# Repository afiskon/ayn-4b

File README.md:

# AYN/4B

Portable QRP CW Transceiver

* Covers 40, 30, 20 and 17 meters
* Classical single IF superheterodyne design
* Has just a few barely hearable (~S0) spurious signals
* Simple but effective AGC
* Supports RIT and XIT
* 10-30 WPM Elekey-B type keyer + straight key mode
* Keyer supports record and playback, programmable with paddles
* ~5W class D power amplifier
* Has a VCC indicator and a SWR meter
* PCB is designed to fit into Hammond 1590BB enclosure
* The project is 100% open-source

Links:
* Article (in Russian): https://eax.me/2023/2023-05-01-ayn-4b-transceiver.html
* Demo: https://www.youtube.com/watch?v=IM0qo4IA7QQ
* Fork by Kirill, R2AXZ with CMake support: https://github.com/r2axz/ayn-4b

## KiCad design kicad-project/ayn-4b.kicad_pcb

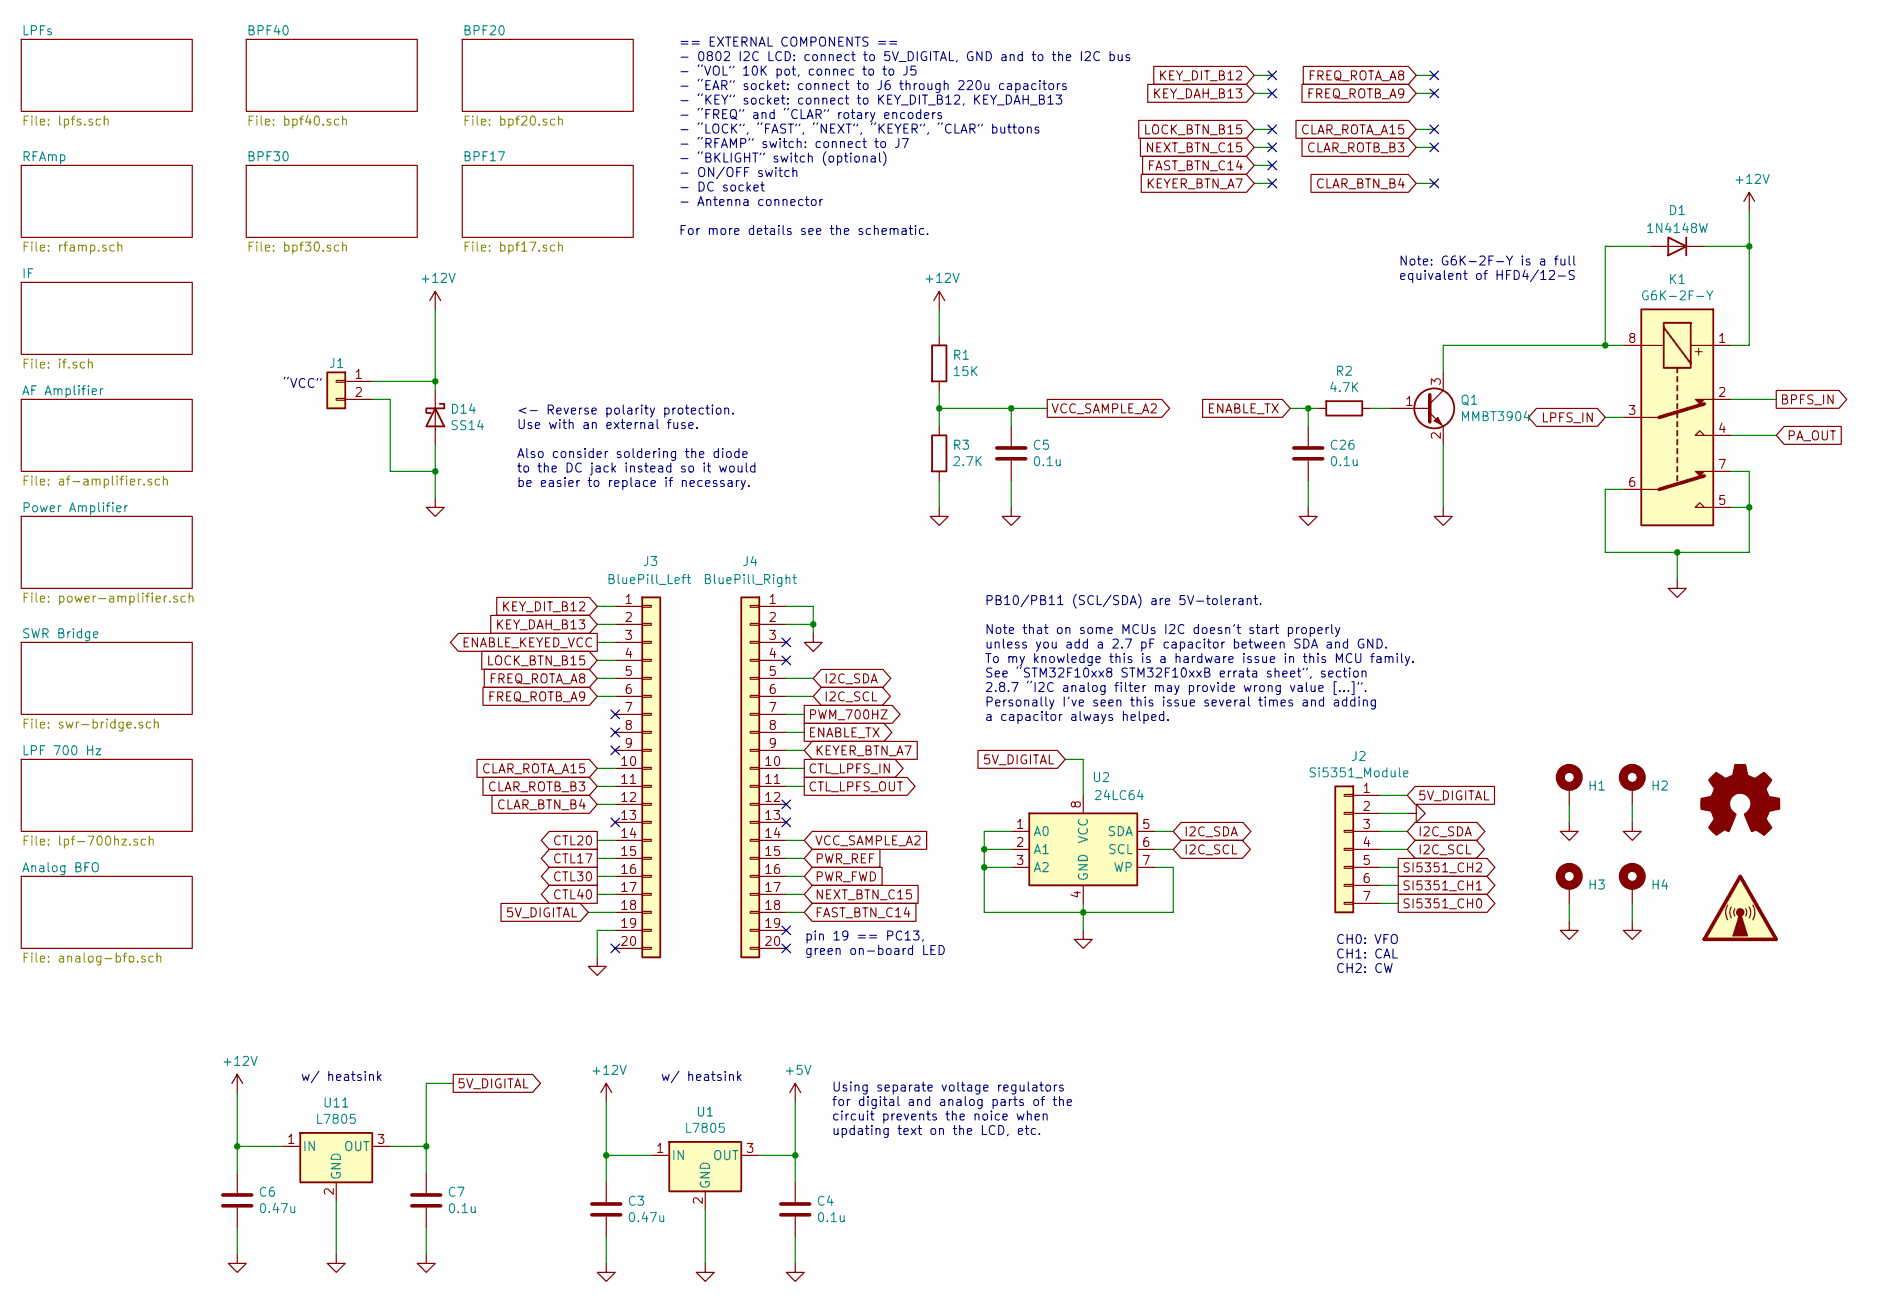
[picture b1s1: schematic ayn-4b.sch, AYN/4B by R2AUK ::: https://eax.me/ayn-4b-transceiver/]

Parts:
C3, C6: 0.47u; C_0805_2012Metric_Pad1.15x1.40mm_HandSolder
C4, C5, C7, C26: 0.1u; C_0805_2012Metric_Pad1.15x1.40mm_HandSolder
D1: 1N4148W; D_SOD-123
D14: SS14; D_SMA_Handsoldering
H1, H2, H3, H4: MountingHole_Pad; MountingHole_M3_Pad_Large
J1: Conn_01x02; PinSocket_1x02_P2.54mm_Vertical
J2: Si5351_Module; PinSocket_1x07_P2.54mm_Vertical
J3: BluePill_Left; PinSocket_1x20_P2.54mm_Vertical
J4: BluePill_Right; PinSocket_1x20_P2.54mm_Vertical
K1: G6K-2F-Y; Relay_DPDT_Omron_G6K-2F-Y
Q1: MMBT3904; SOT-23
R1: 15K; R_0805_2012Metric_Pad1.15x1.40mm_HandSolder
R2: 4.7K; R_0805_2012Metric_Pad1.15x1.40mm_HandSolder
R3: 2.7K; R_0805_2012Metric_Pad1.15x1.40mm_HandSolder
SYM1: Logo_Open_Hardware_Small; OSHW-Logo2_14.6x12mm_SilkScreen
SYM2: SYM_Radio_Waves_Large; KiCad-Logo_5mm_SilkScreen
U1: L7805; TO-220-3_Vertical
U2: 24LC64; SO-8_5.3x6.2mm_P1.27mm
U11: L7805; TO-263-2

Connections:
5V_DIGITAL: C7.1, J2.1, J3.18, U2.8 (VCC), U11.3 (OUT)
+5V: C4.1, U1.3 (OUT); also elsewhere on the board
+12V: C3.1, C6.1, D1.1 (K), D14.1 (K), J1.1, K1.1, R1.1, U1.1 (IN), U11.1 (IN); also elsewhere on the board
BPFS_IN: K1.2; also elsewhere on the board
CLAR_BTN_B4: J3.12
CLAR_ROTA_A15: J3.10
CLAR_ROTB_B3: J3.11
CTL17: J3.15; also elsewhere on the board
CTL20: J3.14; also elsewhere on the board
CTL30: J3.16; also elsewhere on the board
CTL40: J3.17; also elsewhere on the board
CTL_LPFS_IN: J4.10; also elsewhere on the board
CTL_LPFS_OUT: J4.11; also elsewhere on the board
ENABLE_KEYED_VCC: J3.3; also elsewhere on the board
ENABLE_TX: C26.1, J4.8, R2.2
FAST_BTN_C14: J4.18
FREQ_ROTA_A8: J3.5
FREQ_ROTB_A9: J3.6
GND: C3.2, C4.2, C5.2, C6.2, C7.2, C26.2, D14.2 (A), H1.1, H2.1, H3.1, H4.1, J1.2, J2.2, J3.19, J4.1, J4.2, K1.5, K1.6, K1.7, Q1.2 (E), R3.2, U1.2 (GND), U2.1 (A0), U2.2 (A1), U2.3 (A2), U2.4 (GND), U2.7 (WP), U11.2 (GND); also elsewhere on the board
I2C_SCL: J2.4, J4.6, U2.6 (SCL)
I2C_SDA: J2.3, J4.5, U2.5 (SDA)
KEYER_BTN_A7: J4.9
KEY_DAH_B13: J3.2
KEY_DIT_B12: J3.1
LOCK_BTN_B15: J3.4
LPFS_IN: K1.3; also elsewhere on the board
NEXT_BTN_C15: J4.17
unnamed: D1.2 (A), K1.8, Q1.3 (C)
unnamed: Q1.1 (B), R2.1
PA_OUT: K1.4; also elsewhere on the board
PWM_700HZ: J4.7; also elsewhere on the board
PWR_FWD: J4.16; also elsewhere on the board
PWR_REF: J4.15; also elsewhere on the board
SI5351_CH0: J2.7; also elsewhere on the board
SI5351_CH1: J2.6
SI5351_CH2: J2.5; also elsewhere on the board
VCC_SAMPLE_A2: C5.1, J4.14, R1.2, R3.1

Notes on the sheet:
CH0: VFO CH1: CAL CH2: CW
== EXTERNAL COMPONENTS == - 0802 I2C LCD: connect to 5V_DIGITAL, GND and to the I2C bus - “VOL” 10K pot, connec to to J5 - “EAR” socket: connect to J6 through 220u capacitors - “KEY” socket: connect to KEY_DIT_B12, KEY_DAH_B13 - “FREQ” and “CLAR” rotary encoders - “LOCK”, “FAST”, “NEXT”, “KEYER”, “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
w/ heatsink
Note: G6K-2F-Y is a full equivalent of HFD4/12-S
<- Reverse polarity protection. Use with an external fuse. Also consider soldering the diode to the DC jack instead so it would be easier to replace if necessary.
Using separate voltage regulators for digital and analog parts of the circuit prevents the noice when updating text on the LCD, etc.
“VCC”
PB10/PB11 (SCL/SDA) are 5V-tolerant. Note that on some MCUs I2C doesn’t start properly unless you add a 2.7 pF capacitor between SDA and GND. To my knowledge this is a hardware issue in this MCU family. See “STM32F10xx8 STM32F10xxB errata sheet”, section 2.8.7 “I2C analog filter may provide wrong v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
pin 19 == PC13, green on-board LED

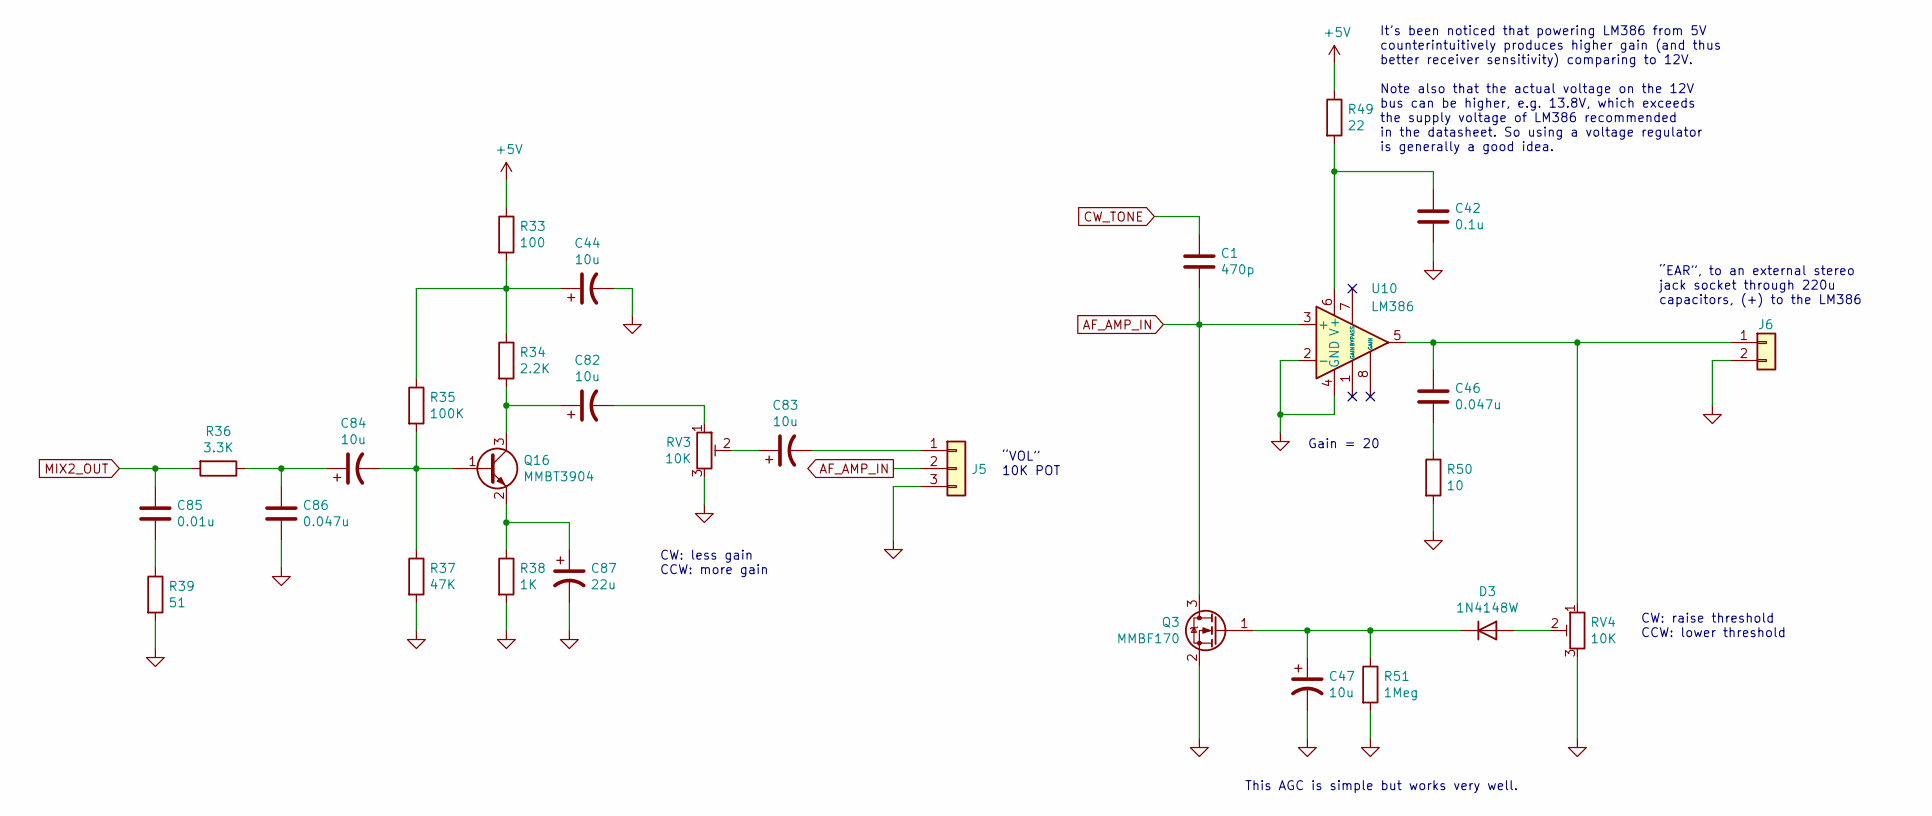
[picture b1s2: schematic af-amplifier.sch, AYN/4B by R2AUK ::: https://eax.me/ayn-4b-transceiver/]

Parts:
C1: 470p; C_0805_2012Metric_Pad1.15x1.40mm_HandSolder
C42: 0.1u; C_0805_2012Metric_Pad1.15x1.40mm_HandSolder
C44, C47, C82, C83, C84: 10u; CP_Elec_4x5.4
C46, C86: 0.047u; C_0805_2012Metric_Pad1.15x1.40mm_HandSolder
C85: 0.01u; C_0805_2012Metric_Pad1.15x1.40mm_HandSolder
C87: 22u; CP_Elec_5x5.4
D3: 1N4148W; D_SOD-123
J5: Conn_01x03; PinSocket_1x03_P2.54mm_Vertical
J6: Conn_01x02; PinSocket_1x02_P2.54mm_Vertical
Q3: MMBF170; SOT-23
Q16: MMBT3904; SOT-23
R33: 100; R_0805_2012Metric_Pad1.15x1.40mm_HandSolder
R34: 2.2K; R_0805_2012Metric_Pad1.15x1.40mm_HandSolder
R35: 100K; R_0805_2012Metric_Pad1.15x1.40mm_HandSolder
R36: 3.3K; R_0805_2012Metric_Pad1.15x1.40mm_HandSolder
R37: 47K; R_0805_2012Metric_Pad1.15x1.40mm_HandSolder
R38: 1K; R_0805_2012Metric_Pad1.15x1.40mm_HandSolder
R39: 51; R_0805_2012Metric_Pad1.15x1.40mm_HandSolder
R49: 22; R_0805_2012Metric_Pad1.15x1.40mm_HandSolder
R50: 10; R_0805_2012Metric_Pad1.15x1.40mm_HandSolder
R51: 1Meg; R_0805_2012Metric_Pad1.15x1.40mm_HandSolder
RV3, RV4: 10K; Potentiometer_Bourns_3296W_Vertical
U10: LM386; SO-8_5.3x6.2mm_P1.27mm

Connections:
+5V: R33.1, R49.1; also elsewhere on the board
AF_AMP_IN: C1.2, J5.2, Q3.3 (D), U10.3 (+)
CW_TONE: C1.1; also elsewhere on the board
GND: C42.2, C44.2, C47.2, C86.2, C87.2, J5.3, J6.2, Q3.2 (S), R37.2, R38.2, R39.2, R50.2, R51.2, RV3.3, RV4.3, U10.2 (-), U10.4 (GND); also elsewhere on the board
MIX2_OUT: C85.1, R36.2; also elsewhere on the board
unnamed: C42.1, R49.2, U10.6 (V+)
unnamed: C44.1, R33.2, R34.1, R35.1
unnamed: C46.1, J6.1, RV4.1, U10.5
unnamed: C46.2, R50.1
unnamed: C47.1, D3.1 (K), Q3.1 (G), R51.1
unnamed: C82.1, Q16.3 (C), R34.2
unnamed: C82.2, RV3.1
unnamed: C83.1, RV3.2
unnamed: C83.2, J5.1
unnamed: C84.1, C86.1, R36.1
unnamed: C84.2, Q16.1 (B), R35.2, R37.1
unnamed: C85.2, R39.1
unnamed: C87.1, Q16.2 (E), R38.1
unnamed: D3.2 (A), RV4.2

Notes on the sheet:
“EAR”, to an external stereo jack socket through 220u capacitors, (+) to the LM386
It’s been noticed that powering LM386 from 5V counterintuitively produces higher gain (and thus better receiver sensitivity) comparing to 12V. Note also that the actual voltage on the 12V bus can be higher, e.g. 13.8V, which exceeds the supply voltage of LM386 recommended in the datasheet. So using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
Gain = 20
This AGC is simple but works very well.
“VOL” 10K POT
CW: less gain CCW: more gain
CW: raise threshold CCW: lower threshold

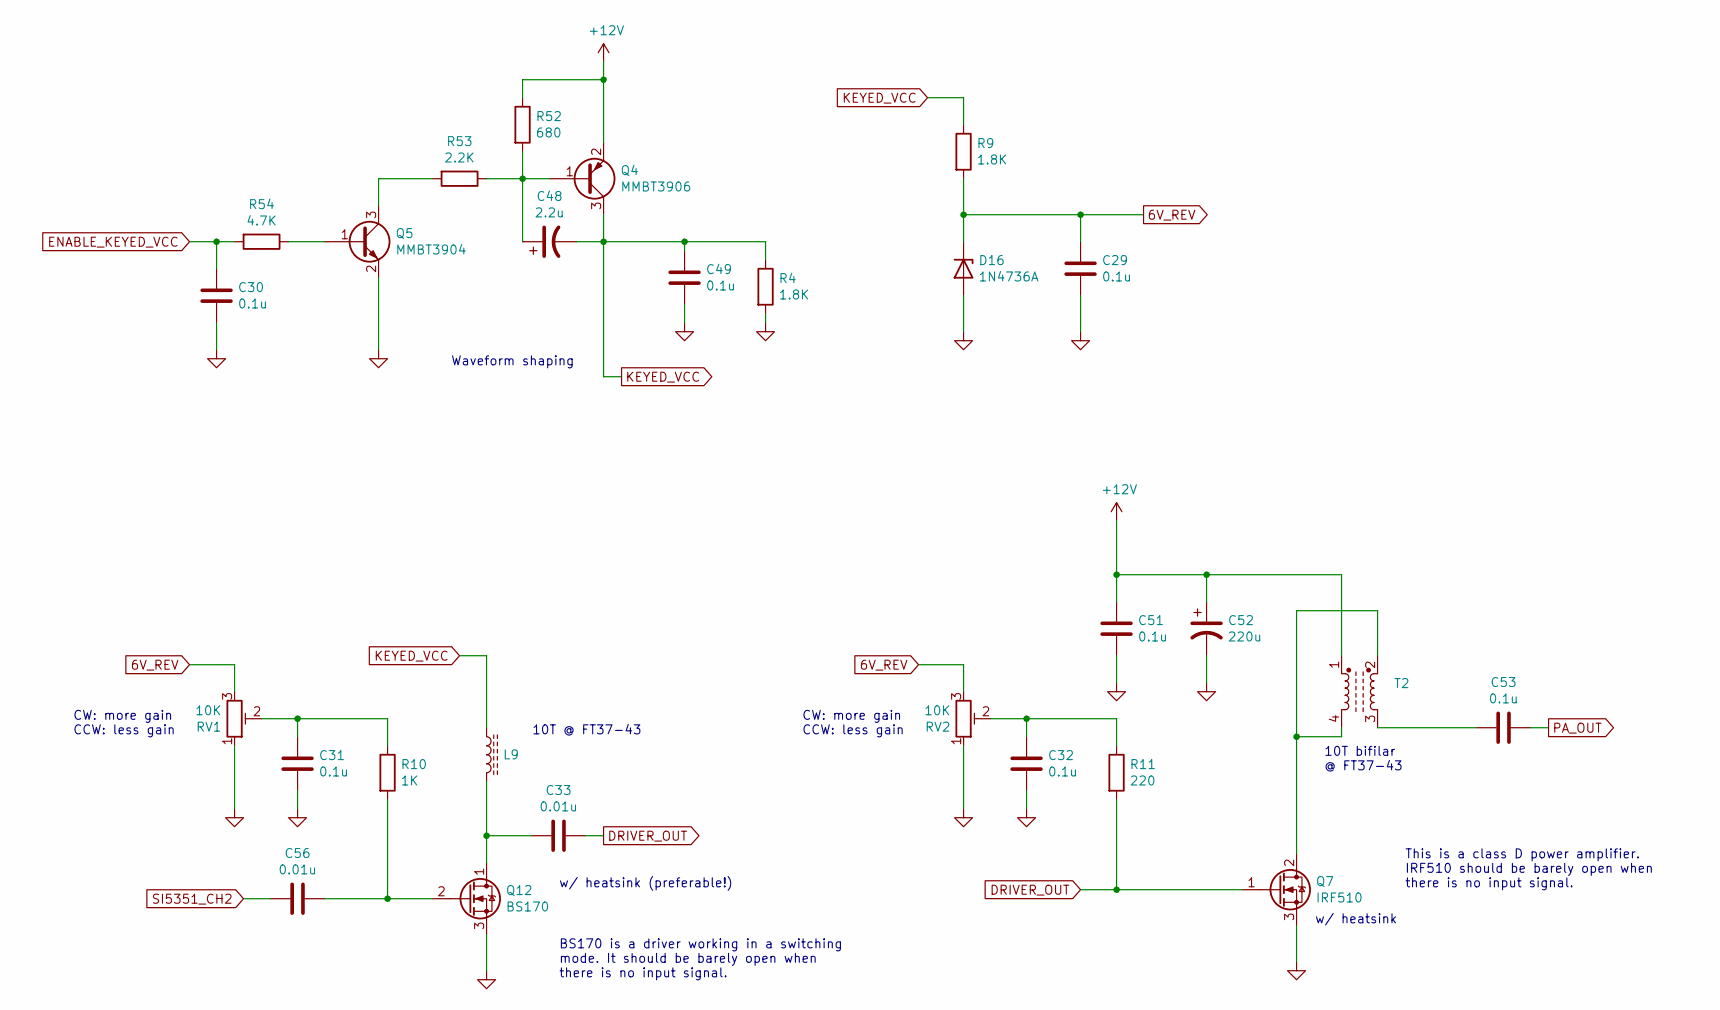
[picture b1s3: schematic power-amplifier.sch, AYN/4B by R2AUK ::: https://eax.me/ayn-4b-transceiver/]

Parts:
C29, C30, C31, C32, C49, C51, C53: 0.1u; C_0805_2012Metric_Pad1.15x1.40mm_HandSolder
C33, C56: 0.01u; C_0805_2012Metric_Pad1.15x1.40mm_HandSolder
C48: 2.2u; CP_Elec_4x5.4
C52: 220u; CP_Elec_8x10.5
D16: 1N4736A; D_DO-41_SOD81_P2.54mm_Vertical_AnodeUp
L9: FT37-43; Toroid_T37_Vertical_THD_L7.0mm_W6.5mm_P5.00mm
Q4: MMBT3906; SOT-23
Q5: MMBT3904; SOT-23
Q7: IRF510; TO-220-3_Vertical
Q12: BS170; TO-92_HandSolder
R4, R9: 1.8K; R_0805_2012Metric_Pad1.15x1.40mm_HandSolder
R10: 1K; R_0805_2012Metric_Pad1.15x1.40mm_HandSolder
R11: 220; R_0805_2012Metric_Pad1.15x1.40mm_HandSolder
R52: 680; R_0805_2012Metric_Pad1.15x1.40mm_HandSolder
R53: 2.2K; R_0805_2012Metric_Pad1.15x1.40mm_HandSolder
R54: 4.7K; R_0805_2012Metric_Pad1.15x1.40mm_HandSolder
RV1, RV2: 10K; Potentiometer_Bourns_3296W_Vertical
T2: FT37-43; DIP-4_W7.62mm

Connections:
6V_REV: C29.1, D16.1 (K), R9.2, RV1.3, RV2.3
+12V: C51.1, C52.1, Q4.2 (E), R52.1, T2.1; also elsewhere on the board
DRIVER_OUT: C33.1, Q7.1 (G), R11.2
ENABLE_KEYED_VCC: C30.1, R54.2; also elsewhere on the board
GND: C29.2, C30.2, C31.2, C32.2, C49.2, C51.2, C52.2, D16.2 (A), Q5.2 (E), Q7.3 (S), Q12.3 (S), R4.2, RV1.1, RV2.1; also elsewhere on the board
KEYED_VCC: C48.2, C49.1, L9.1, Q4.3 (C), R4.1, R9.1
unnamed: C31.1, R10.1, RV1.2
unnamed: C32.1, R11.1, RV2.2
unnamed: C33.2, L9.2, Q12.1 (D)
unnamed: C48.1, Q4.1 (B), R52.2, R53.1
unnamed: C53.2, T2.3
unnamed: C56.1, Q12.2 (G), R10.2
unnamed: Q5.1 (B), R54.1
unnamed: Q5.3 (C), R53.2
unnamed: Q7.2 (D), T2.2, T2.4
PA_OUT: C53.1; also elsewhere on the board
SI5351_CH2: C56.2; also elsewhere on the board

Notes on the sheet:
10T bifilar @ FT37-43
Waveform shaping
10T @ FT37-43
w/ heatsink
CW: more gain CCW: less gain
BS170 is a driver working in a switching mode. It should be barely open when there is no input signal.
This is a class D power amplifier. IRF510 should be barely open when there is no input signal.
w/ heatsink (preferable!)

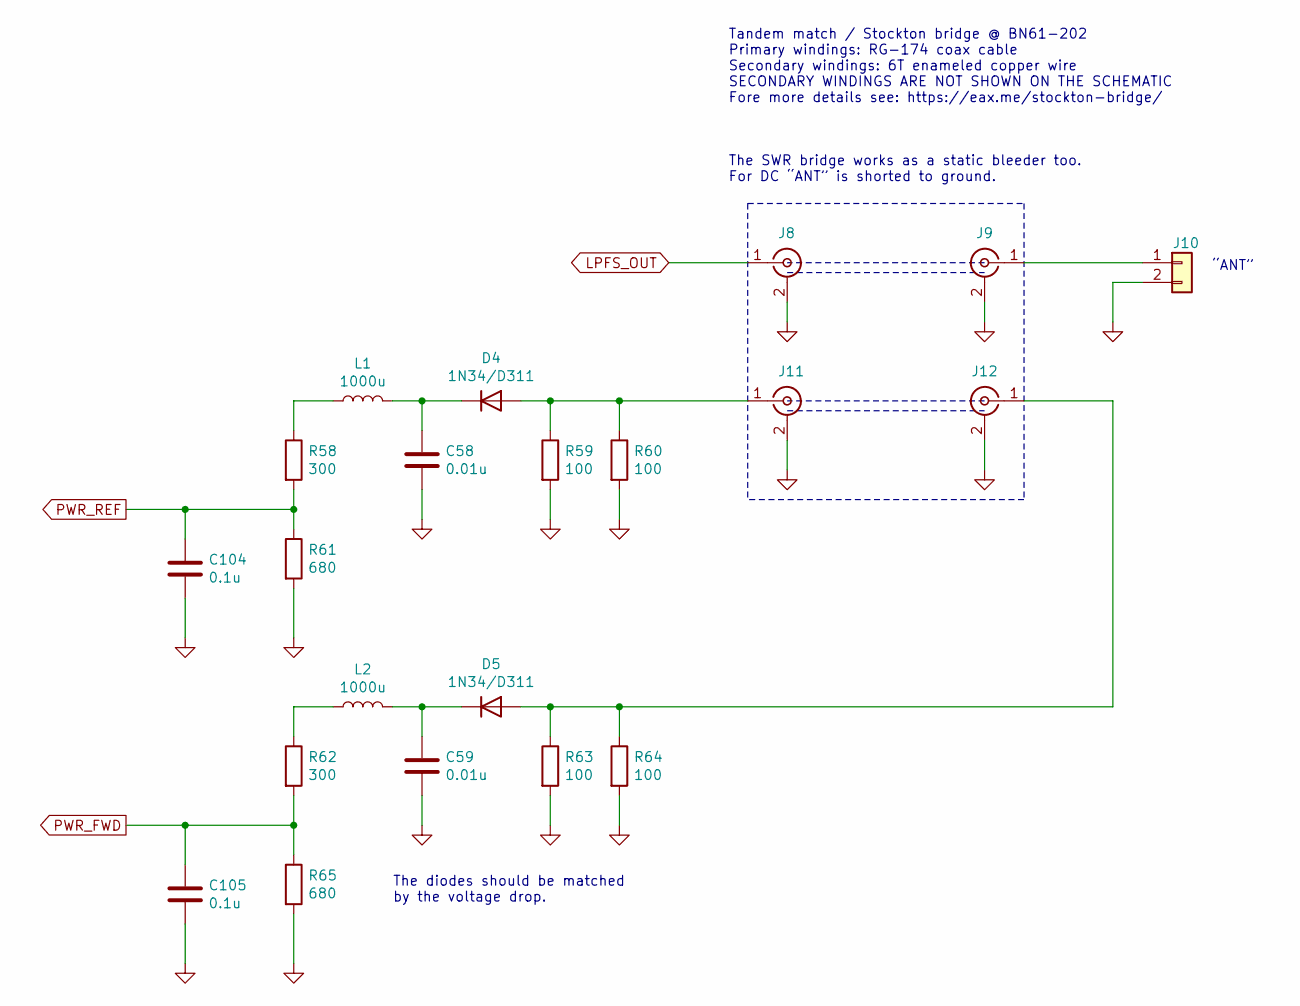
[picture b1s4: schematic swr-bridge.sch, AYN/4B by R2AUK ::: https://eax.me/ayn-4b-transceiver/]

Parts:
C58, C59: 0.01u; C_0805_2012Metric_Pad1.15x1.40mm_HandSolder
C104, C105: 0.1u; C_0805_2012Metric_Pad1.15x1.40mm_HandSolder
D4, D5: 1N34/D311; D_DO-41_SOD81_P2.54mm_Vertical_AnodeUp
J8, J9, J11, J12: Conn_Coaxial; PinSocket_1x02_P2.54mm_Vertical
J10: Conn_01x02; PinSocket_1x02_P2.54mm_Vertical
L1, L2: 1000u; D_DO-41_SOD81_P2.54mm_Vertical_AnodeUp
R58, R62: 300; R_0805_2012Metric_Pad1.15x1.40mm_HandSolder
R59, R60, R63, R64: 100; R_0805_2012Metric_Pad1.15x1.40mm_HandSolder
R61, R65: 680; R_0805_2012Metric_Pad1.15x1.40mm_HandSolder

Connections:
GND: C58.2, C59.2, C104.2, C105.2, J8.2 (Ext), J9.2 (Ext), J10.2, J11.2 (Ext), J12.2 (Ext), R59.2, R60.2, R61.2, R63.2, R64.2, R65.2; also elsewhere on the board
LPFS_OUT: J8.1 (In); also elsewhere on the board
unnamed: C58.1, D4.1 (K), L1.2
unnamed: C59.1, D5.1 (K), L2.2
unnamed: D4.2 (A), J11.1 (In), R59.1, R60.1
unnamed: D5.2 (A), J12.1 (In), R63.1, R64.1
unnamed: J9.1 (In), J10.1
unnamed: L1.1, R58.1
unnamed: L2.1, R62.1
PWR_FWD: C105.1, R62.2, R65.1; also elsewhere on the board
PWR_REF: C104.1, R58.2, R61.1; also elsewhere on the board

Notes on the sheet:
“ANT”
The SWR bridge works as a static bleeder too. For DC “ANT” is shorted to ground.
Tandem match / Stockton bridge @ BN61-202 Primary windings: RG-174 coax cable Secondary windings: 6T enameled copper wire SECONDARY WINDINGS ARE NOT SHOWN ON THE SCHEMATIC Fore more details see: https://eax.me/stockton-bridge/
The diodes should be matched by the voltage drop.

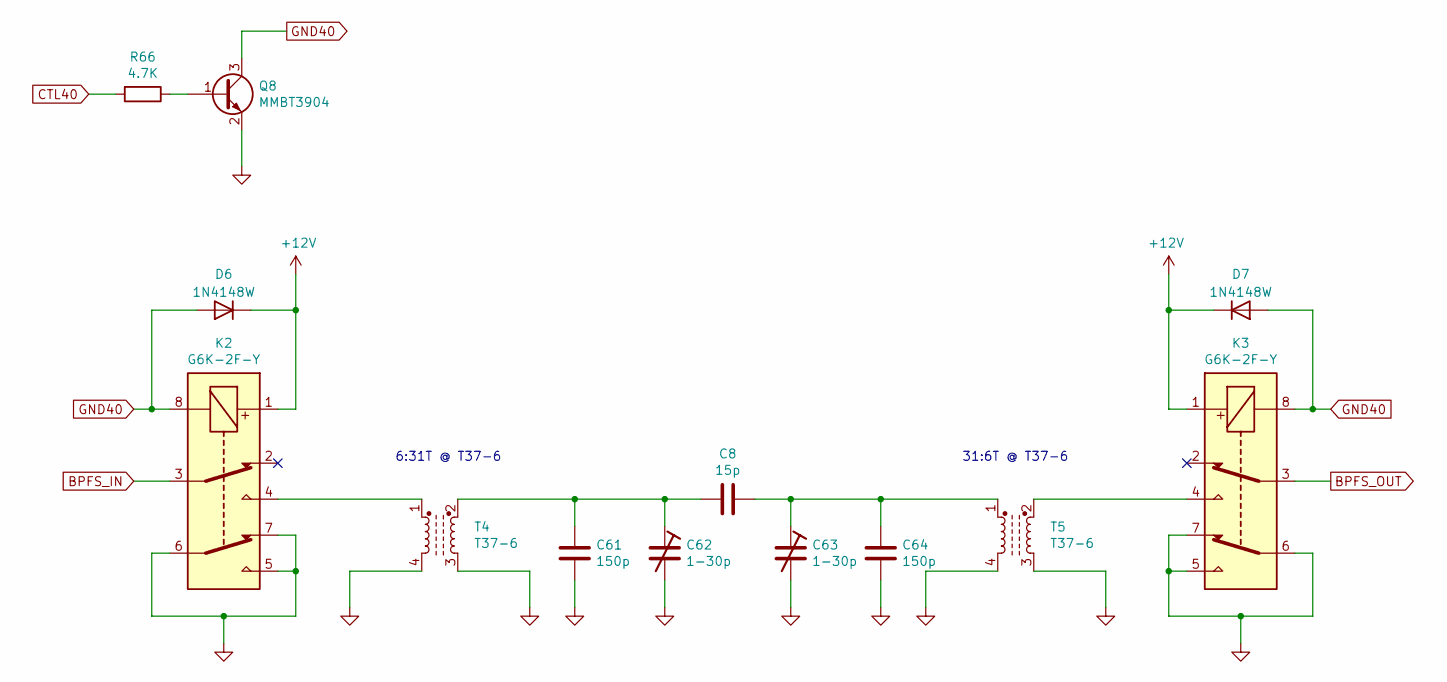
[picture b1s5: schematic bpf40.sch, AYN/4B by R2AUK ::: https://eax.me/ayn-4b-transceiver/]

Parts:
C8: 15p; C_0805_2012Metric_Pad1.15x1.40mm_HandSolder
C61, C64: 150p; C_0805_2012Metric_Pad1.15x1.40mm_HandSolder
C62, C63: 1-30p; C_Trim_THD_L7.0mm_W6.5mm_P5.00mm
D6, D7: 1N4148W; D_SOD-123
K2, K3: G6K-2F-Y; Relay_DPDT_Omron_G6K-2F-Y
Q8: MMBT3904; SOT-23
R66: 4.7K; R_0805_2012Metric_Pad1.15x1.40mm_HandSolder
T4, T5: T37-6; DIP-4_W7.62mm

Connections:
+12V: D6.1 (K), D7.1 (K), K2.1, K3.1; also elsewhere on the board
BPFS_IN: K2.3; also elsewhere on the board
BPFS_OUT: K3.3; also elsewhere on the board
CTL40: R66.2; also elsewhere on the board
GND: C61.2, C62.2, C63.2, C64.2, K2.5, K2.6, K2.7, K3.5, K3.6, K3.7, Q8.2 (E), T4.3, T4.4, T5.3, T5.4; also elsewhere on the board
GND40: D6.2 (A), D7.2 (A), K2.8, K3.8, Q8.3 (C)
unnamed: C8.2, C61.1, C62.1, T4.2
unnamed: C8.1, C63.1, C64.1, T5.1
unnamed: K2.4, T4.1
unnamed: K3.4, T5.2
unnamed: Q8.1 (B), R66.1

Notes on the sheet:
6:31T @ T37-6
31:6T @ T37-6

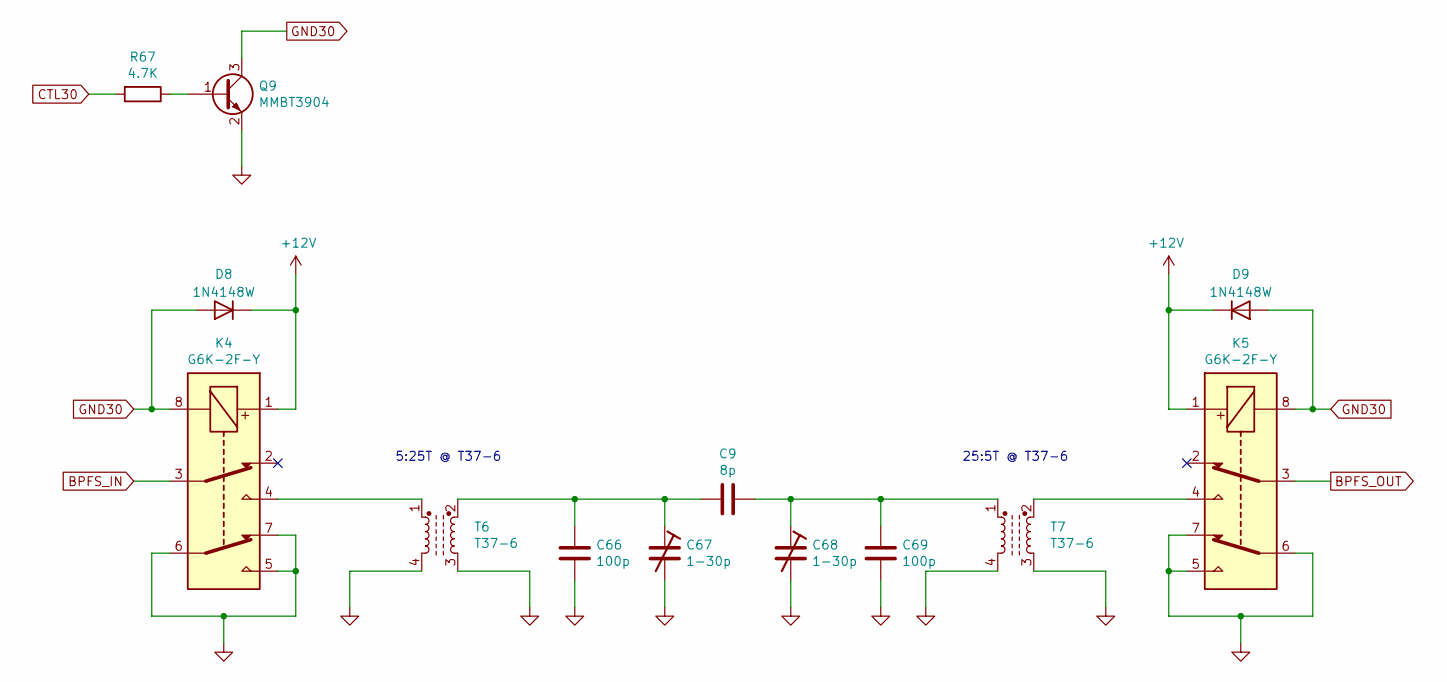
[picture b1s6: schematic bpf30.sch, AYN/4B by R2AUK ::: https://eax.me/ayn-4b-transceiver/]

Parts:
C9: 8p; C_0805_2012Metric_Pad1.15x1.40mm_HandSolder
C66, C69: 100p; C_0805_2012Metric_Pad1.15x1.40mm_HandSolder
C67, C68: 1-30p; C_Trim_THD_L7.0mm_W6.5mm_P5.00mm
D8, D9: 1N4148W; D_SOD-123
K4, K5: G6K-2F-Y; Relay_DPDT_Omron_G6K-2F-Y
Q9: MMBT3904; SOT-23
R67: 4.7K; R_0805_2012Metric_Pad1.15x1.40mm_HandSolder
T6, T7: T37-6; DIP-4_W7.62mm

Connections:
+12V: D8.1 (K), D9.1 (K), K4.1, K5.1; also elsewhere on the board
BPFS_IN: K4.3; also elsewhere on the board
BPFS_OUT: K5.3; also elsewhere on the board
CTL30: R67.2; also elsewhere on the board
GND: C66.2, C67.2, C68.2, C69.2, K4.5, K4.6, K4.7, K5.5, K5.6, K5.7, Q9.2 (E), T6.3, T6.4, T7.3, T7.4; also elsewhere on the board
GND30: D8.2 (A), D9.2 (A), K4.8, K5.8, Q9.3 (C)
unnamed: C9.2, C66.1, C67.1, T6.2
unnamed: C9.1, C68.1, C69.1, T7.1
unnamed: K4.4, T6.1
unnamed: K5.4, T7.2
unnamed: Q9.1 (B), R67.1

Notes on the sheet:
5:25T @ T37-6
25:5T @ T37-6

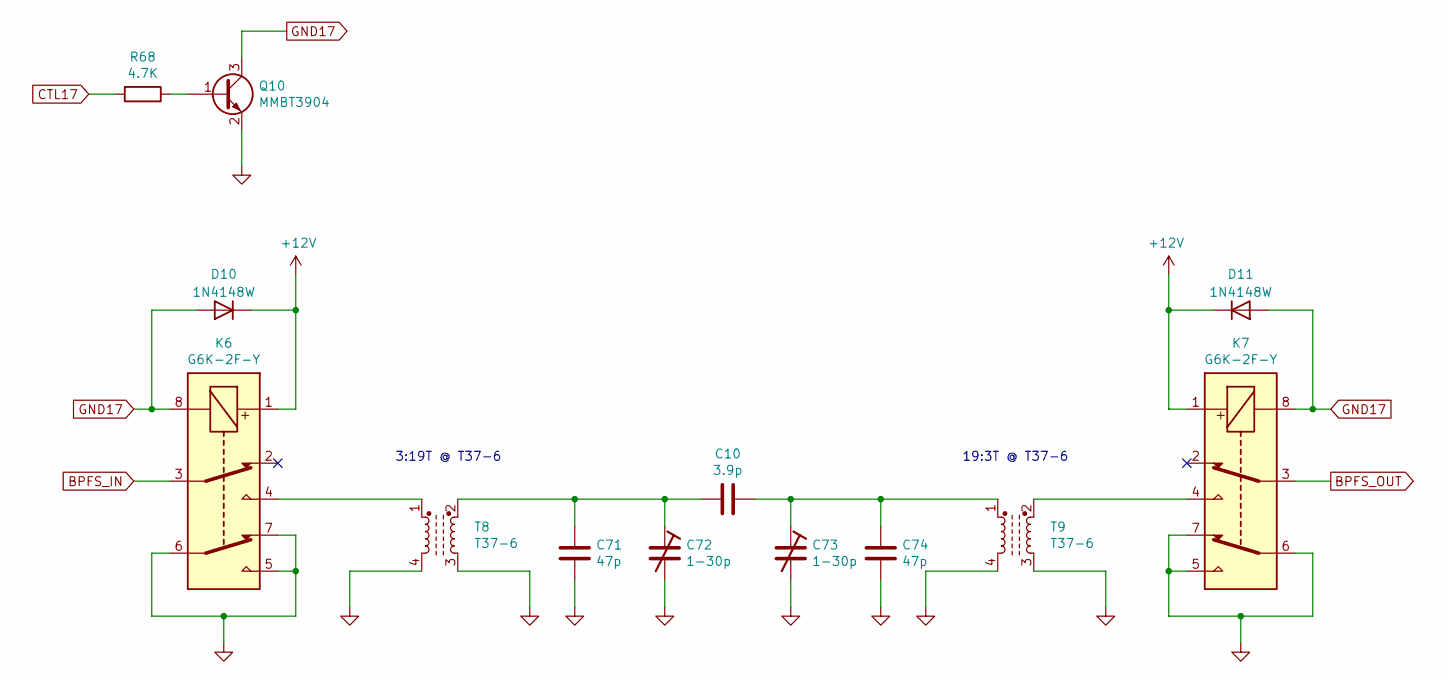
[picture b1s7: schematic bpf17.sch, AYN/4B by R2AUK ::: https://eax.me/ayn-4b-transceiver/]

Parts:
C10: 3.9p; C_0805_2012Metric_Pad1.15x1.40mm_HandSolder
C71, C74: 47p; C_0805_2012Metric_Pad1.15x1.40mm_HandSolder
C72, C73: 1-30p; C_Trim_THD_L7.0mm_W6.5mm_P5.00mm
D10, D11: 1N4148W; D_SOD-123
K6, K7: G6K-2F-Y; Relay_DPDT_Omron_G6K-2F-Y
Q10: MMBT3904; SOT-23
R68: 4.7K; R_0805_2012Metric_Pad1.15x1.40mm_HandSolder
T8, T9: T37-6; DIP-4_W7.62mm

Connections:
+12V: D10.1 (K), D11.1 (K), K6.1, K7.1; also elsewhere on the board
BPFS_IN: K6.3; also elsewhere on the board
BPFS_OUT: K7.3; also elsewhere on the board
CTL17: R68.2; also elsewhere on the board
GND: C71.2, C72.2, C73.2, C74.2, K6.5, K6.6, K6.7, K7.5, K7.6, K7.7, Q10.2 (E), T8.3, T8.4, T9.3, T9.4; also elsewhere on the board
GND17: D10.2 (A), D11.2 (A), K6.8, K7.8, Q10.3 (C)
unnamed: C10.1, C73.1, C74.1, T9.1
unnamed: C10.2, C71.1, C72.1, T8.2
unnamed: K6.4, T8.1
unnamed: K7.4, T9.2
unnamed: Q10.1 (B), R68.1

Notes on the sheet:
3:19T @ T37-6
19:3T @ T37-6

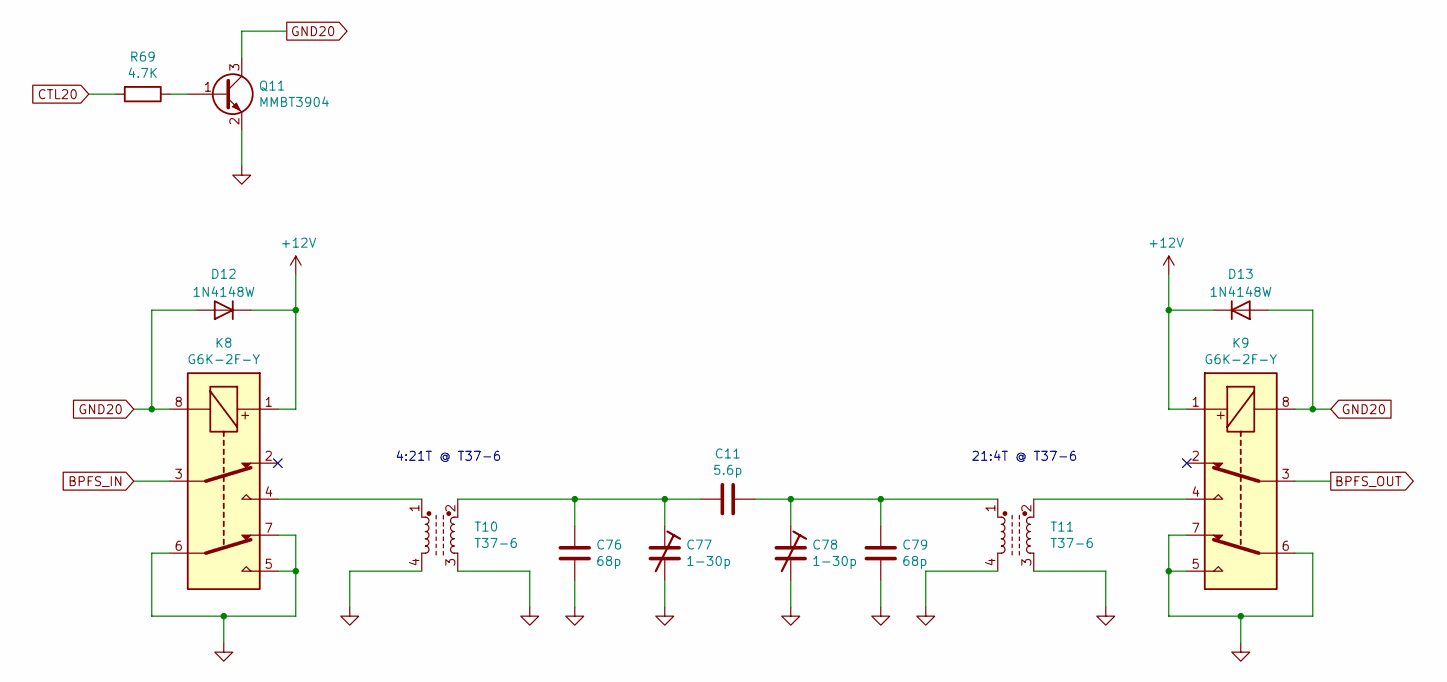
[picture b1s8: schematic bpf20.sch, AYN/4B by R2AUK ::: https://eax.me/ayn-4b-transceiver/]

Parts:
C11: 5.6p; C_0805_2012Metric_Pad1.15x1.40mm_HandSolder
C76, C79: 68p; C_0805_2012Metric_Pad1.15x1.40mm_HandSolder
C77, C78: 1-30p; C_Trim_THD_L7.0mm_W6.5mm_P5.00mm
D12, D13: 1N4148W; D_SOD-123
K8, K9: G6K-2F-Y; Relay_DPDT_Omron_G6K-2F-Y
Q11: MMBT3904; SOT-23
R69: 4.7K; R_0805_2012Metric_Pad1.15x1.40mm_HandSolder
T10, T11: T37-6; DIP-4_W7.62mm

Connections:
+12V: D12.1 (K), D13.1 (K), K8.1, K9.1; also elsewhere on the board
BPFS_IN: K8.3; also elsewhere on the board
BPFS_OUT: K9.3; also elsewhere on the board
CTL20: R69.2; also elsewhere on the board
GND: C76.2, C77.2, C78.2, C79.2, K8.5, K8.6, K8.7, K9.5, K9.6, K9.7, Q11.2 (E), T10.3, T10.4, T11.3, T11.4; also elsewhere on the board
GND20: D12.2 (A), D13.2 (A), K8.8, K9.8, Q11.3 (C)
unnamed: C11.1, C78.1, C79.1, T11.1
unnamed: C11.2, C76.1, C77.1, T10.2
unnamed: K8.4, T10.1
unnamed: K9.4, T11.2
unnamed: Q11.1 (B), R69.1

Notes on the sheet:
4:21T @ T37-6
21:4T @ T37-6

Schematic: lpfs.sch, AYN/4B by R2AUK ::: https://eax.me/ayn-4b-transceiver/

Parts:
C12, C25: 68p; C_0805_2012Metric_Pad1.15x1.40mm_HandSolder
C13, C15, C16, C17: 330p; C_0805_2012Metric_Pad1.15x1.40mm_HandSolder
C14: 220p; C_0805_2012Metric_Pad1.15x1.40mm_HandSolder
C18, C20, C21, C22, C23, C24: 150p; C_0805_2012Metric_Pad1.15x1.40mm_HandSolder
C19: 33p; C_0805_2012Metric_Pad1.15x1.40mm_HandSolder
C27, C28: 0.1u; C_0805_2012Metric_Pad1.15x1.40mm_HandSolder
D2, D15: 1N4148W; D_SOD-123
K10, K11: G6K-2F-Y; Relay_DPDT_Omron_G6K-2F-Y
L3, L4, L5, L6, L7, L8: T37-6; Toroid_T37_Vertical_THD_L7.0mm_W6.5mm_P5.00mm
Q2, Q6: MMBT3904; SOT-23
R5, R6: 4.7K; R_0805_2012Metric_Pad1.15x1.40mm_HandSolder

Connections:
+12V: D2.1 (K), D15.1 (K), K10.1, K11.1; also elsewhere on the board
CTL_LPFS_IN: C27.1, R5.2; also elsewhere on the board
CTL_LPFS_OUT: C28.1, R6.2; also elsewhere on the board
GND: C15.2, C16.2, C17.2, C18.2, C22.2, C23.2, C24.2, C25.2, C27.2, C28.2, K10.5, K10.6, K10.7, K11.5, K11.6, K11.7, Q2.2 (E), Q6.2 (E); also elsewhere on the board
GND_LPFS_IN: D2.2 (A), K10.8, Q2.3 (C)
GND_LPFS_OUT: D15.2 (A), K11.8, Q6.3 (C)
LPFS_IN: K10.3; also elsewhere on the board
LPFS_OUT: K11.3; also elsewhere on the board
LPF_20_17_IN: C19.2, C22.1, K10.4, L6.1
LPF_20_17_OUT: C21.1, C25.1, K11.2, L8.2
LPF_40_30_IN: C12.2, C15.1, K10.2, L3.1
LPF_40_30_OUT: C14.1, C18.1, K11.4, L5.2
unnamed: C12.1, C13.2, C16.1, L3.2, L4.1
unnamed: C13.1, C14.2, C17.1, L4.2, L5.1
unnamed: C19.1, C20.2, C23.1, L6.2, L7.1
unnamed: C20.1, C21.2, C24.1, L7.2, L8.1
unnamed: Q2.1 (B), R5.1
unnamed: Q6.1 (B), R6.1

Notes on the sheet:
16T @ T37-6
12T @ T37-6
13T @ T37-6
11T @ T37-6
8T @ T37-6
9T @ T37-6

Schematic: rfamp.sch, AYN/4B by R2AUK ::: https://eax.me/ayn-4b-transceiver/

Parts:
C2, C34, C35, C36, C37: 0.1u; C_0805_2012Metric_Pad1.15x1.40mm_HandSolder
D17: 1N4148W; D_SOD-123
J7: Conn_01x02; PinSocket_1x02_P2.54mm_Vertical
K12: G6K-2F-Y; Relay_DPDT_Omron_G6K-2F-Y
Q13: MMBT3904; SOT-23
R12: 22; R_0805_2012Metric_Pad1.15x1.40mm_HandSolder
R13: 3.3K; R_0805_2012Metric_Pad1.15x1.40mm_HandSolder
R14: 1.3K; R_0805_2012Metric_Pad1.15x1.40mm_HandSolder
R15: 68; R_0805_2012Metric_Pad1.15x1.40mm_HandSolder
R16: 1K; R_0805_2012Metric_Pad1.15x1.40mm_HandSolder
R17: 6.2; R_0805_2012Metric_Pad1.15x1.40mm_HandSolder
T1: FT37-43; DIP-4_W7.62mm

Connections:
+12V: D17.1 (K), K12.1, R12.1; also elsewhere on the board
BPFS_OUT: K12.3; also elsewhere on the board
GND: C2.2, J7.2, R15.2, R16.2, R17.2; also elsewhere on the board
MIX1_IN: K12.6; also elsewhere on the board
unnamed: C2.1, R12.2, T1.2
unnamed: C34.1, Q13.3 (C), R13.1, T1.4
unnamed: C34.2, R13.2, R14.1
unnamed: C35.2, T1.1, T1.3
unnamed: C36.1, Q13.1 (B), R14.2, R16.1
unnamed: C37.1, Q13.2 (E), R15.1
unnamed: C37.2, R17.1
unnamed: D17.2 (A), J7.1, K12.8
RFAMP_BYPASS: K12.4, K12.5
RFAMP_IN: C36.2, K12.2
RFAMP_OUT: C35.1, K12.7

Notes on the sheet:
“RFAMP” switch
10T bifilar @ FT37-43

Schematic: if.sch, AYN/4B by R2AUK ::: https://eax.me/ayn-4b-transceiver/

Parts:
C38, C39, C40, C41, C43, C45, C50, C54, C55, C57, C81: 0.1u; C_0805_2012Metric_Pad1.15x1.40mm_HandSolder
C60, C65, C70, C75, C80, C98: 270p; C_0805_2012Metric_Pad1.15x1.40mm_HandSolder
C93, C94: 470p; C_0805_2012Metric_Pad1.15x1.40mm_HandSolder
C95, C96: 220p; C_0805_2012Metric_Pad1.15x1.40mm_HandSolder
L10, L11: T37-6; L_Toroid_Horizontal_D9.5mm_P15.00mm_Diameter10-5mm_Amidon-T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
Q14, Q15: MMBT3904; SOT-23
R18, R19: 22; R_0805_2012Metric_Pad1.15x1.40mm_HandSolder
R20, R22: 3.3K; R_0805_2012Metric_Pad1.15x1.40mm_HandSolder
R21, R23: 1.3K; R_0805_2012Metric_Pad1.15x1.40mm_HandSolder
R24, R26: 68; R_0805_2012Metric_Pad1.15x1.40mm_HandSolder
R25, R27: 1K; R_0805_2012Metric_Pad1.15x1.40mm_HandSolder
R28, R29: 6.2; R_0805_2012Metric_Pad1.15x1.40mm_HandSolder
R30, R31: 150; R_0805_2012Metric_Pad1.15x1.40mm_HandSolder
R32: 36; R_0805_2012Metric_Pad1.15x1.40mm_HandSolder
T3, T12: FT37-43; DIP-4_W7.62mm
U3, U4: ADE-6; Mini-Circuits_CD542_LandPatternPL-052
Y1, Y2, Y3, Y4, Y5: 9.000; Crystal_HC49-U_Vertical

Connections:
+12V: R18.1, R19.1; also elsewhere on the board
ANALOG_BFO: C93.1, L10.1; also elsewhere on the board
ATT_IN: C50.1, R30.2, R32.1
BUFFER_IN: C54.2, U3.2 (IF)
GND: C38.2, C39.2, C70.2, C75.2, C80.2, C93.2, C94.2, C95.2, C96.2, C98.2, R24.2, R25.2, R26.2, R27.2, R28.2, R29.2, R30.1, R31.1, U3.1 (GND), U3.4 (GND), U3.5 (GND), U4.1 (GND), U4.4 (GND), U4.5 (GND); also elsewhere on the board
IFAMP_IN: C65.1, Q14.1 (B), R21.2, R25.1
IFAMP_OUT: C45.1, U4.3 (RF)
MIX1_IN: U3.3 (RF); also elsewhere on the board
MIX2_OUT: U4.2 (IF); also elsewhere on the board
unnamed: C38.1, R18.2, T3.2
unnamed: C39.1, R19.2, T12.2
unnamed: C40.1, Q14.3 (C), R20.1, T3.4
unnamed: C40.2, R20.2, R21.1
unnamed: C41.1, U3.6 (LO)
unnamed: C41.2, C96.1, L11.2
unnamed: C43.1, Q15.3 (C), R22.1, T12.4
unnamed: C43.2, R22.2, R23.1
unnamed: C45.2, T3.1, T3.3
unnamed: C50.2, T12.1, T12.3
unnamed: C54.1, Q15.1 (B), R23.2, R27.1
unnamed: C55.1, Q14.2 (E), R24.1
unnamed: C55.2, R28.1
unnamed: C57.1, Q15.2 (E), R26.1
unnamed: C57.2, R29.1
unnamed: C60.1, Y1.1
unnamed: C65.2, Y5.2
unnamed: C70.1, Y1.2, Y2.1
unnamed: C75.1, Y2.2, Y3.1
unnamed: C80.1, Y3.2, Y4.1
unnamed: C81.1, U4.6 (LO)
unnamed: C81.2, C94.1, L10.2
unnamed: C98.1, Y4.2, Y5.1
SI5351_CH0: C95.1, L11.1; also elsewhere on the board
XFLTR_IN: C60.2, R31.2, R32.2

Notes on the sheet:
10T bifilar @ FT37-43
6 dB attenuator
High-Q (>= 100 000) crystals are required to get a narrowband CW filter with low losses. The crystals should be measured using G3UUR method and matched by the resonant frequency. Use LTspice to find the right capacitance for your crystals.
16T @ T37-6
7T @ T37-6
VFO
LPF 30 MHz
LPF 11 MHz

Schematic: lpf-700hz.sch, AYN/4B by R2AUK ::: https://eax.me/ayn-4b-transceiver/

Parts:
C88, C89, C90, C91, C92, C97: 0.1u; C_0805_2012Metric_Pad1.15x1.40mm_HandSolder
R40, R45: 100K; R_0805_2012Metric_Pad1.15x1.40mm_HandSolder
R41, R42, R43, R44: 1.8K; R_0805_2012Metric_Pad1.15x1.40mm_HandSolder
U5: NE5532; SOIC-8_5.23x5.23mm_P1.27mm

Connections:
+5V: C97.1, R40.1, U5.8 (V+); also elsewhere on the board
CW_TONE: C89.1, U5.6 (-), U5.7; also elsewhere on the board
GND: C91.2, C92.2, C97.2, R45.2, U5.4 (V-); also elsewhere on the board
unnamed: C88.1, R41.2, U5.1, U5.2 (-)
unnamed: C88.2, R43.1, R44.2
unnamed: C89.2, R41.1, R42.2
unnamed: C90.1, R40.2, R43.2, R45.1
unnamed: C91.1, R44.1, U5.3 (+)
unnamed: C92.1, R42.1, U5.5 (+)
PWM_700HZ: C90.2; also elsewhere on the board
